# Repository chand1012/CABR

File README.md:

# CABR

The CABR (Pronounced KAY-BER) is a 3D printed Nerf Computerized Adaptive Bullpup Rifle for full length darts.

# Features

- Simple design: only 8 printed parts for the blaster.
- Toolless access to the battery compartment, flywheel cage and barrel.
- Dual stage trigger.
- 41.5mm flywheel gap for the integral flywheel cage.
- Full length dart feed guide.
- FTW solenoid pusher.
- Full length picatinny top rail.
- Optional side picatinny rails.
- Integrated sling mounts.
- Computerized Semi, Burst, and Automatic modes.
- Battery buzzer for power detection.

# Required Parts

|Part            |Quantity  |Description                                                       |
|----------------|----------|------------------------------------------------------------------|
|Flywheel motors |2         |130 or 180 sized motors for flywheels [Purchase Link](https://outofdarts.com/collections/motors-2019/products/ood-kraken-motor) |
|Flywheels       |2         |Flywheels [Purchase Link](https://outofdarts.com/collections/flywheels-cages/products/containment-crew-inferno-flywheels-pair) |
|FTW Solenoid    |1         |FTW Solenoid for the pusher [Purchase Link](https://www.banggood.com/DC-12V-35mm-Long-Stroke-Push-Pull-Solenoid-Small-Electromagnetic-Electric-Magnet-p-1217063.html?cur_warehouse=CN) |
|Microswitch              | 2 | For activating the motors and solenoid [Purchase Link](https://outofdarts.com/collections/electronics/products/21a-microswitch-button-clone)                        |
|Silicone insulated wire  |   | Wiring [Purchase Link](https://www.amazon.com/BNTECHGO-Silicone-Flexible-Strands-Stranded/dp/B01C5CANVG/ref=pd_lpo_sbs_60_t_2?_encoding=UTF8&psc=1&refRID=DZD6XCXG9PDEQ4CW3V4W)                                                        |
|Heat set threaded inserts| 10 | To hold in screws (McMaster 94180A333 for 100)                |
|Compression Spring       | 1 | For trigger (McMaster 9657K56 for 12)                          |
|Torsion Spring           | 1 | For magazine release (McMaster 9271K579 for 6)                 |
|M4x10 Socket head screw  | 1 | For securing the solenoid                                      |
|M3x10 Socket head screws | 7 |                                                                |
|M3x25 Socket head screws | 2 | Used for flywheel switch and trigger                           |
|M3x35 Socket head screw  | 1 | For magazine release                                           |
|M2 screws                | 4 | For motors                                                     |
|2 1/2" x 3/16" Pins      | 3 | For securing the battery and stock (McMaster 98330A125 for 10) |

# Additional Parts for circuitry

|Quantity|Ref Des       |Desc               |Part #                 |Manufacterer                   |Link                                                                                                            |
|--------|--------------|-------------------|-----------------------|-------------------------------|----------------------------------------------------------------------------------------------------------------|
|1       |U1            |Attiny85-20SU      |Attiny85-20SU          |Atmel                          |[Digikey](https://www.digikey.com/product-detail/en/microchip-technology/ATTINY85-20SU/ATTINY85-20SU-ND/735470)            |
|1       |Q1            |Solenoid Transistor|PBSS4250X,115          |NXP                            |[Digikey](https://www.digikey.com/product-detail/en/nexperia-usa-inc/PBSS4250X115/1727-5750-1-ND/2697143)                  |
|1       |U2            |Voltage Reg        |AZ1117CH-5.0TRG1DICT-ND|Diodes Inc                     |[Digikey](https://www.digikey.com/product-detail/en/diodes-incorporated/AZ1117CH-5.0TRG1/AZ1117CH-5.0TRG1DICT-ND/4505207)  |
|1       |D2            |Solenoid Diode     |MMSD4148T3GOSTR-ND     |ON Semi                        |[Digikey](https://www.digikey.com/product-detail/en/on-semiconductor/MMSD4148T3G/MMSD4148T3GOSCT-ND/1967161)               |
|1       |C1            |Filter Cap         |EMK212BBJ106MGHT       |Taiyo Yuden                    |[Digikey](https://www.digikey.com/product-detail/en/taiyo-yuden/EMK212BBJ106MGHT/587-6311-1-ND/9949897)                    |
|1       |D1            |Status LED         |LTST-C171GKT           |Lite-On Inc                    |[Digikey](https://www.digikey.com/product-detail/en/lite-on-inc/LTST-C171GKT/160-1423-1-ND/386792)                         |
|4       |R1, R2, R4, R5|Resistor           |RNCP0805FTD10K0        |Stackpole Electronics          |[Digikey](https://www.digikey.com/product-detail/en/stackpole-electronics-inc/RNCP0805FTD10K0/RNCP0805FTD10K0CT-ND/2240601)|
|1       |R3            |Resistor           |CRG0805F2K7            |TE Connectivity Passive Product|[Digikey](https://www.digikey.com/product-detail/en/te-connectivity-passive-product/CRG0805F2K7/A126359CT-ND/7603414)      |
|1       |R6            |Resistor           |RR1220P-102-D          |Susumu                         |[Digikey](https://www.digikey.com/product-detail/en/susumu/RR1220P-102-D/RR12P1.0KDCT-ND/432830)                           |
|1       |C3            |MicroController Cap|CL21F104ZBCNNNC        |Samsung Electro-Mechanics      |[Digikey](https://www.digikey.com/product-detail/en/samsung-electro-mechanics/CL21F104ZBCNNNC/1276-1007-1-ND/3889093)      |
|1       |C2            |Filter Cap         |TMK212BBJ106KG-T       |Taiyo Yuden                    |[Digikey](https://www.digikey.com/product-detail/en/taiyo-yuden/TMK212BBJ106KG-T/587-2985-1-ND/2714178)                    |
|1       |J2            |Fire Mode Switch   |SS-13D16-VG 4 PA       |C&K                            |[Digikey](https://www.digikey.com/product-detail/en/SS-13D16-VG+4+PA/CKN10371-ND/2747181)                                  |

# Printing Parameters

Prototypes were printed using these parameters:

- PLA
- .3mm layer height
- .4mm nozzle
- 1.2mm vertical wall thickness
/- No supports (Except for the back of the reciever)

# Assembly

[Assembly guide on the repository wiki](https://github.com/chand1012/SABR/wiki/Assembly)

# Contributing

The project was designed using Fusion 360, under their hobbyist license.

# Attributions

This project uses the [FTW Solenoid by FlywheelTheWorld](https://www.thingiverse.com/thing:3518739) and the [FTW Solenoid Pusher Head by FlywheelTheWorld](https://www.thingiverse.com/thing:3307908).

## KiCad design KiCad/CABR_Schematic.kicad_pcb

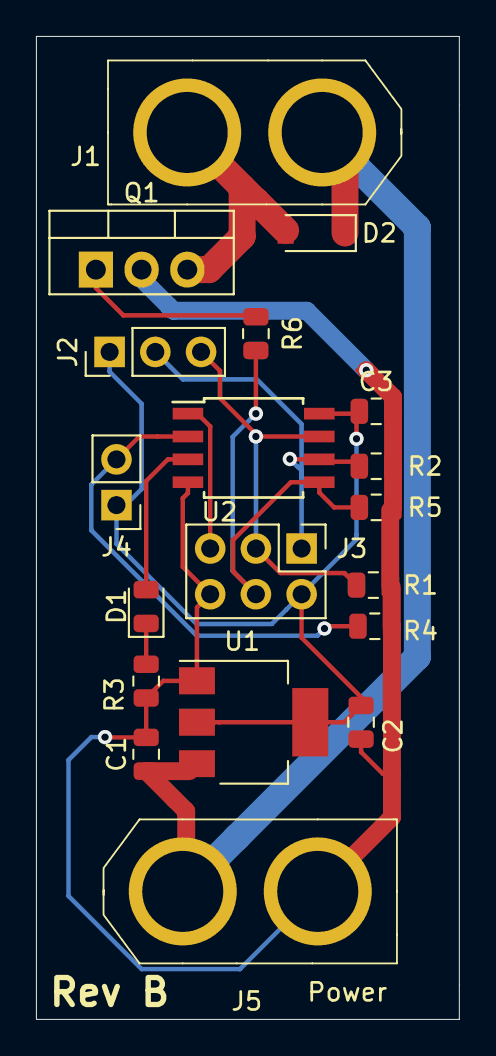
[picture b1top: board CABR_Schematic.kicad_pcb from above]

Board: 2 copper layers, 23.5 x 54.6 mm, 19 parts (0 on the bottom side), 12 nets.

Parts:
C1, C2: 10uF; C_0805_2012Metric
C3: 0.1uF; C_0805_2012Metric
D1: Green; LED_0805_2012Metric
D2: MMSD4148T3G; D_SOD-123
J1, J5: XT60
J2: 0.1" Header; PinHeader_1x03_P2.54mm_Vertical
J3: Program Header; PinHeader_2x03_P2.54mm_Vertical
J4: MicroSwitch; PinHeader_1x02_P2.54mm_Vertical
Q1: FQP30N06L; TO-220-3_Vertical
R1, R2, R4, R5: 10k; R_0805_2012Metric
R3: 2.7k; R_0805_2012Metric
R6: 1k; R_0805_2012Metric
U1: AZ1117-5.0; SOT-223-3_TabPin2
U2: ATtiny85-20SU; SOIJ-8_5.3x5.3mm_P1.27mm

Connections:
GND: C1.2, C2.2, C3.2, J3.6, J5.2, Q1.2, R1.1, R2.2, R3.2, R4.2, R5.1, U1.1, U2.4
unnamed: C1.1, D2.1, J1.1, J5.1, U1.3
unnamed: C2.1, C3.1, J2.1, J3.2, J4.1, U1.2, U2.8
unnamed: D1.1, R3.1
unnamed: D1.2, U2.3
unnamed: D2.2, J1.2, Q1.3
unnamed: J2.2, J3.1, R2.1, U2.6
unnamed: J2.3, J3.3, R1.2, U2.7
unnamed: J3.4, R5.2, R6.1, U2.5
unnamed: J3.5, U2.1
unnamed: J4.2, R4.1, U2.2
unnamed: Q1.1, R6.2

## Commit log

2019-07-15 added main arduino file and to gitignore
2019-07-16 finalized arduino code
2019-07-16 Added Fire ready indicator
2019-07-16 added schematic pdf
2019-07-16 added more to README
2019-07-16 Added CABR Back Reciever File
2019-07-16 Added nifty parts reciever
2019-07-16 fixed non manifold issue
2019-07-16 removed SABR rear
2019-07-18 moved some files around
2019-07-18 fixed rear barrel scaling
2019-07-18 minor code changes
2019-07-18 fixed schematic
2019-07-18 change micro to attiny85
2019-07-18 Added fritzing board layout
2019-07-18 fixed issues with transistor
2019-07-18 added buy links for the micro
2019-07-19 updated the fritzing perfboard layout
2019-07-19 more fritzing things
2019-07-20 fixed issue with front barrel not fitting rear barrel
2019-07-23 added non nifty reciever
2019-07-23 changed burst and auto mode pins
2019-07-23 Added kicad files
2019-07-24 added prototype code for the board
2019-07-24 got PCB design
2019-07-24 redid file structure
2019-07-24 Edited frizing prototype
2019-07-24 added prototype photo
2019-07-25 fixed issues with prototype
2019-07-25 updated PCB and gerber files
2019-07-25 more pcb changes
2019-07-25 updated PCB again
2019-07-25 added BOM to readme
2019-07-26 things
2019-07-30 edited step file
2019-07-30 Renamed to CABR
2019-07-31 changed code?
2019-07-31 made changes for solenoid output
2019-07-31 modified delay times for solenoid
2019-08-04 added switch slot
2019-08-05 added picture
2019-08-05 added readme picture
2019-08-06 added support block
2019-08-14 updated prototype sketch
2019-08-14 updated block
2019-08-15 Added platformio building
2019-08-20 fixed issue with boardfire
2019-08-21 updated design and fixed output pins
2019-08-21 more board updates
2019-08-21 more modifications
2019-08-22 more fixes
2019-08-22 update schematic
2019-08-22 more updates
2019-09-04 limit "auto" to 22 rounds
